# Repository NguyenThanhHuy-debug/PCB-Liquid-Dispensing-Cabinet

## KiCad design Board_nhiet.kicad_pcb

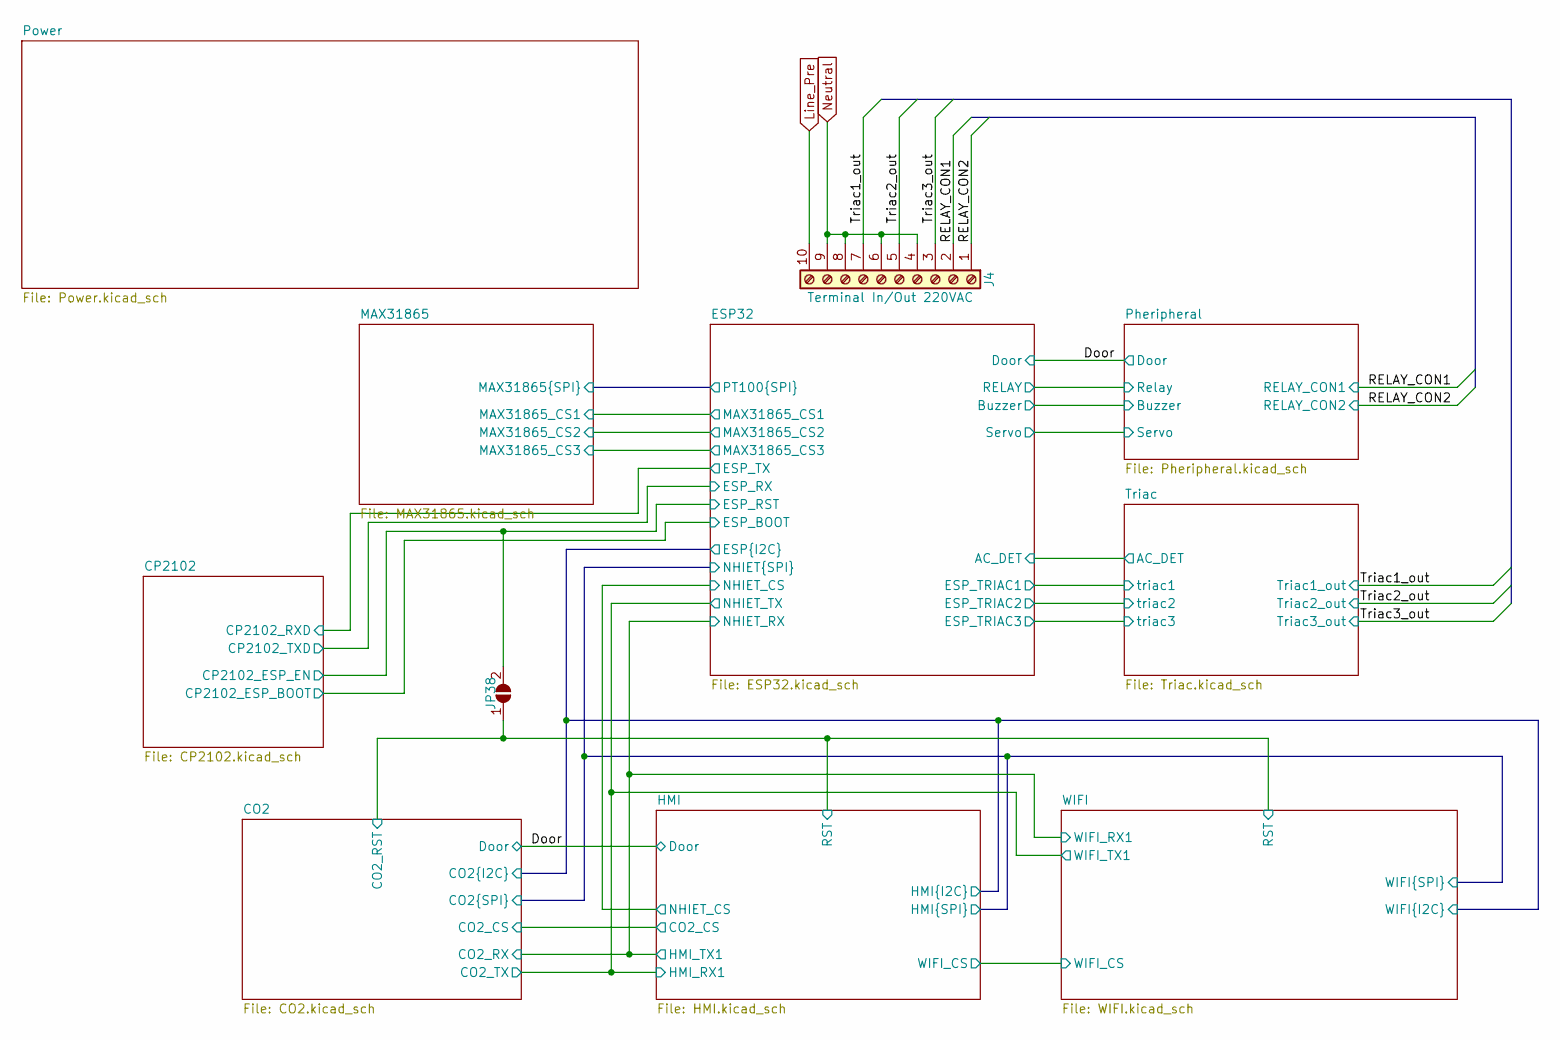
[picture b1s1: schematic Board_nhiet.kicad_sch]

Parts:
J4: Terminal In/Out 220VAC; TerminalBlock_Screw_HB9500_10P_P9.5mm
JP38: SolderJumper_2_Open; SolderJumper-2_P1.3mm_Open_RoundedPad1.0x1.5mm

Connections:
/CO2/CO2_RST: JP38.1 (A); also elsewhere on the board
/ESP32/ESP_RST: JP38.2 (B); also elsewhere on the board
/RELAY_CON1: J4.2; also elsewhere on the board
/RELAY_CON2: J4.1; also elsewhere on the board
/Triac1_out: J4.7; also elsewhere on the board
/Triac2_out: J4.5; also elsewhere on the board
/Triac3_out: J4.3; also elsewhere on the board
Line_Pre: J4.10; also elsewhere on the board
Neutral: J4.4, J4.6, J4.8, J4.9; also elsewhere on the board

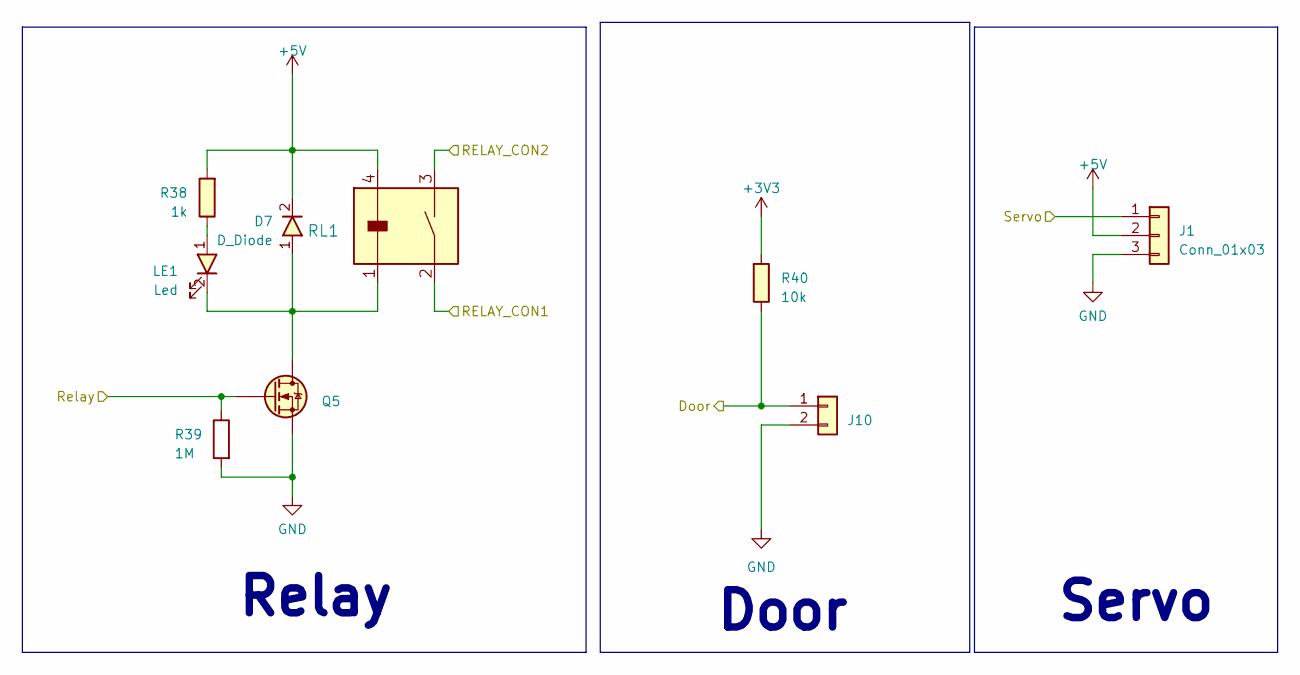
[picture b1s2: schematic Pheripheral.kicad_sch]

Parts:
D7: D_Diode; D_SOD-123
J1: Conn_01x03; Terminal_HT-3.96mm-3P-Vertical-Pluggable
J10: Conn_01x02; Terminal_HT-3.96mm-2P-Vertical-Pluggable
LE1: Led; LED_0603
Q5: N_Mosfet; SOT23-3
R38: 1k; R_0603
R39: 1M; R_0603
R40: 10k; R_0603
RL1: Relay_G5NB-1A-E_DC5; Relay_G5NB-1A-E DC5

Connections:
+3.3V: R40.1; also elsewhere on the board
+5V: D7.2, J1.2, R38.1, RL1.4; also elsewhere on the board
/Door: J10.1, R40.2; also elsewhere on the board
/ESP32/RELAY: Q5.1 (G), R39.1; also elsewhere on the board
/ESP32/Servo: J1.1; also elsewhere on the board
/RELAY_CON1: RL1.2; also elsewhere on the board
/RELAY_CON2: RL1.3; also elsewhere on the board
GND: J1.3, J10.2, Q5.2 (S), R39.2; also elsewhere on the board
unnamed: LE1.1, R38.2
unnamed: D7.1, LE1.2, Q5.3 (D), RL1.1

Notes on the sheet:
Relay
Servo
Door

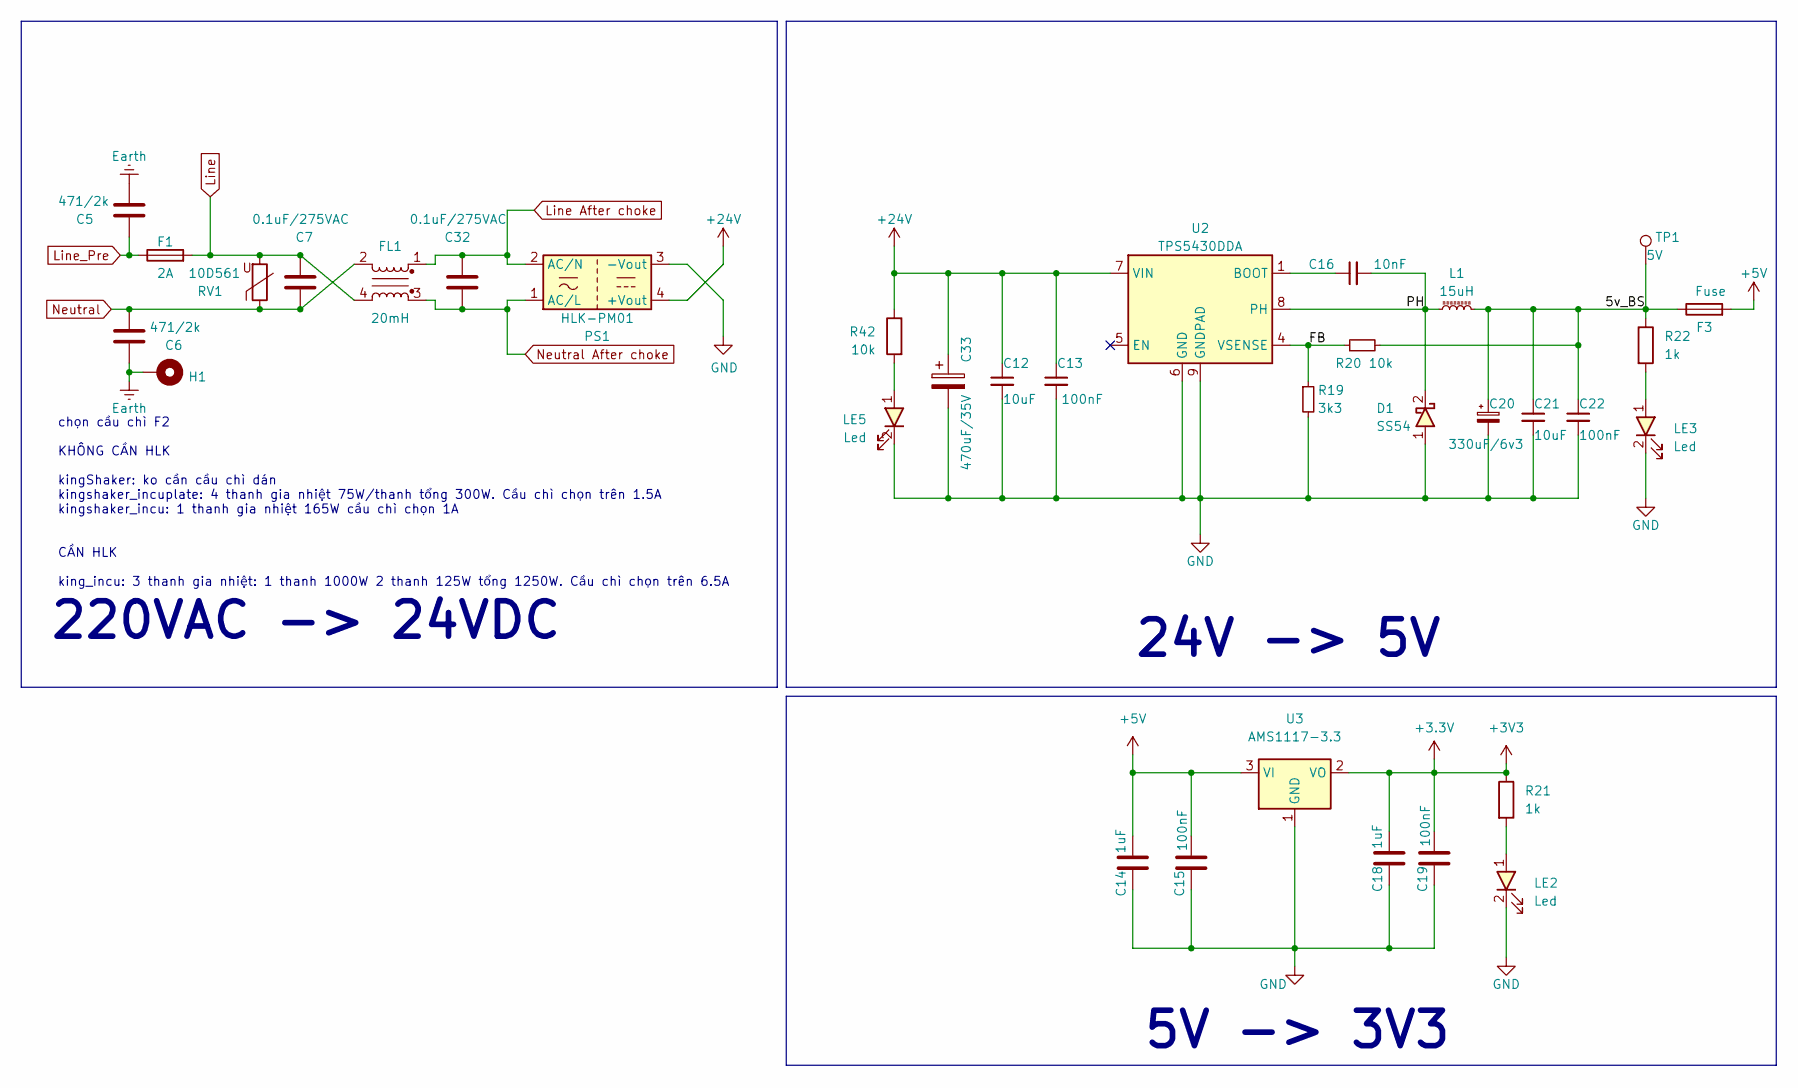
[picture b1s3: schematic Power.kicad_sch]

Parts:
C5, C6: 471/2k; C_Disc_D4.3mm_W1.9mm_P5.00mm
C7, C32: 0.1uF/275VAC; C_Rect_L16.5mm_W5.0mm_P15.00mm_MKT
C12, C21: 10uF; C_0805
C13, C22: 100nF; C_0805
C14, C18: 1uF; C_0603
C15, C19: 100nF; C_0603
C16: 10nF; C_0603
C20: 330uF/6v3; CP_Elec_6.3x7.7
C33: 470uF/35V; CP_Elec_10x10.5
D1: SS54; D_SMA
F1: 2A; Fuse_HolderGlass5x20mm
F3: Fuse; Fuse_1812_4532Metric
FL1: 20mH; ACFilterChokeUU9.8
H1: MountingHole_Pad; MountingHole_3.2mm_M3_Pad_Via
L1: 15uH; L_6.6x6.6
LE2, LE3, LE5: Led; LED_0603
PS1: HLK-PM01; ACDC_HLK-20MXX
R19: 3k3; R_0603
R20, R42: 10k; R_0603
R21, R22: 1k; R_0603
RV1: 10D561; RV_Disc_D12mm_W5.8mm_P7.5mm
TP1: 5V; TestPoint_Pad_D1.0mm
U2: TPS5430DDA; SOIC8E(EXPOSED PAD)
U3: AMS1117-3.3; SOT-223-3_TabPin2

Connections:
+3.3V: C18.2, C19.2, R21.1, U3.2 (VO); also elsewhere on the board
+5V: C14.2, C15.2, F3.2, U3.3 (VI); also elsewhere on the board
+24V: C12.1, C13.1, C33.1, PS1.4 (+Vout), R42.1, U2.7 (VIN); also elsewhere on the board
/Power/5v_BS: C20.1, C21.1, C22.1, F3.1, L1.2, R20.2, R22.1, TP1.1
/Power/FB: R19.1, R20.1, U2.4 (VSENSE)
/Power/PH: C16.2, D1.2, L1.1, U2.8 (PH)
Earth: C5.2, C6.1, H1.1
GND: C12.2, C13.2, C14.1, C15.1, C18.1, C19.1, C20.2, C21.2, C22.2, C33.2, D1.1, LE2.2, LE3.2, LE5.2, PS1.3 (-Vout), R19.2, U2.6 (GND), U2.9 (GNDPAD), U3.1 (GND); also elsewhere on the board
Line: C7.2, F1.2, FL1.4, RV1.2
Line After choke: C32.2, FL1.1, PS1.2 (AC/N); also elsewhere on the board
Line_Pre: C5.1, F1.1; also elsewhere on the board
unnamed: LE2.1, R21.2
unnamed: LE3.1, R22.2
unnamed: LE5.1, R42.2
unnamed: C16.1, U2.1 (BOOT)
Neutral: C6.2, C7.1, FL1.2, RV1.1; also elsewhere on the board
Neutral After choke: C32.1, FL1.3, PS1.1 (AC/L); also elsewhere on the board

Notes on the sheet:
chọn cầu chì F2 KHÔNG CẦN HLK kingShaker: ko cần cầu chì dán kingshaker_incuplate: 4 thanh gia nhiệt 75W/thanh tổng 300W. Cầu chì chọn trên 1.5A kingshaker_incu: 1 thanh gia nhiệt 165W cầu chì chọn 1A CẦN HLK king_incu: 3 thanh gia nhiệt: 1 thanh 1000W 2 thanh 125W tổng 1250W. Cầu chì chọn trên 6.5A
220VAC -> 24VDC
5V -> 3V3
24V -> 5V

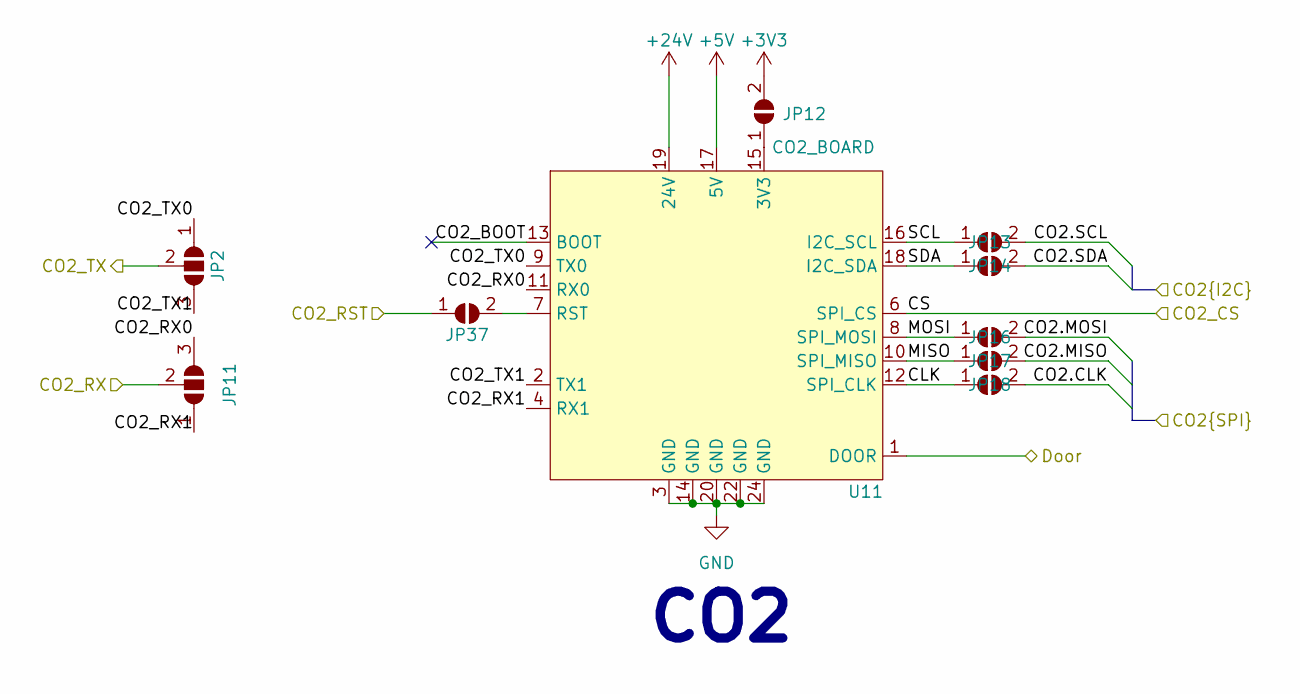
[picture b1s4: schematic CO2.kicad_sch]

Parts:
JP2, JP11: SolderJumper_3_Open; SolderJumper-3_P1.3mm_Open_RoundedPad1.0x1.5mm_NumberLabels
JP12, JP13, JP14, JP16, JP17, JP18, JP37: SolderJumper_2_Open; SolderJumper-2_P1.3mm_Open_RoundedPad1.0x1.5mm
U11: CO2_BOARD; CO2_Board

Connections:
+3.3V: JP12.2 (B); also elsewhere on the board
+5V: U11.17 (5V); also elsewhere on the board
+24V: U11.19 (24V), U11.21 (24V), U11.23 (24V); also elsewhere on the board
/CO2/CLK: JP18.1 (A), U11.12 (SPI_CLK)
/CO2/CO2.CLK: JP18.2 (B); also elsewhere on the board
/CO2/CO2.MISO: JP17.2 (B); also elsewhere on the board
/CO2/CO2.MOSI: JP16.2 (B); also elsewhere on the board
/CO2/CO2.SCL: JP13.2 (B); also elsewhere on the board
/CO2/CO2.SDA: JP14.2 (B); also elsewhere on the board
/CO2/CO2_BOOT: U11.13 (BOOT)
/CO2/CO2_RST: JP37.1 (A); also elsewhere on the board
/CO2/CO2_RX: JP11.2 (C); also elsewhere on the board
/CO2/CO2_RX0: JP11.3 (B), U11.11 (RX0)
/CO2/CO2_RX1: JP11.1 (A), U11.4 (RX1)
/CO2/CO2_TX: JP2.2 (C); also elsewhere on the board
/CO2/CO2_TX0: JP2.1 (A), U11.9 (TX0)
/CO2/CO2_TX1: JP2.3 (B), U11.2 (TX1)
/CO2/CS: U11.6 (SPI_CS); also elsewhere on the board
/CO2/MISO: JP17.1 (A), U11.10 (SPI_MISO)
/CO2/MOSI: JP16.1 (A), U11.8 (SPI_MOSI)
/CO2/SCL: JP13.1 (A), U11.16 (I2C_SCL)
/CO2/SDA: JP14.1 (A), U11.18 (I2C_SDA)
/Door: U11.1 (DOOR); also elsewhere on the board
GND: U11.3 (GND), U11.5 (GND), U11.14 (GND), U11.20 (GND), U11.22 (GND), U11.24 (GND); also elsewhere on the board
unnamed: JP12.1 (A), U11.15 (3V3)
unnamed: JP37.2 (B), U11.7 (RST)

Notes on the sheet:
CO2

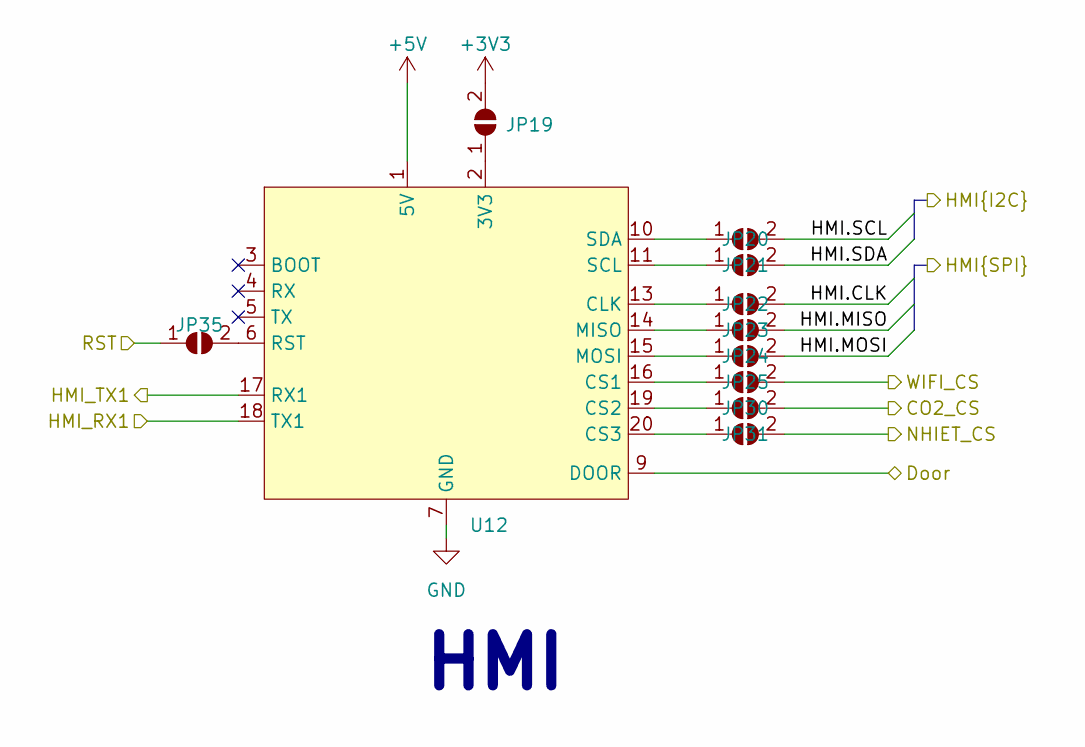
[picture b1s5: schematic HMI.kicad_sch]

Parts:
JP19, JP20, JP21, JP22, JP23, JP24, JP25, JP30, JP31, JP35: SolderJumper_2_Open; SolderJumper-2_P1.3mm_Open_RoundedPad1.0x1.5mm
U12: HMI_BOARD

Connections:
+3.3V: JP19.2 (B); also elsewhere on the board
+5V: U12.1 (5V); also elsewhere on the board
/CO2/CO2.CLK: JP22.2 (B); also elsewhere on the board
/CO2/CO2.MISO: JP23.2 (B); also elsewhere on the board
/CO2/CO2.MOSI: JP24.2 (B); also elsewhere on the board
/CO2/CO2.SCL: JP20.2 (B); also elsewhere on the board
/CO2/CO2.SDA: JP21.2 (B); also elsewhere on the board
/CO2/CO2_RST: JP35.1 (A); also elsewhere on the board
/CO2/CO2_RX: U12.17 (RX1); also elsewhere on the board
/CO2/CO2_TX: U12.18 (TX1); also elsewhere on the board
/CO2/CS: JP30.2 (B); also elsewhere on the board
/Door: U12.9 (DOOR); also elsewhere on the board
/ESP32/NHIET_CS: JP31.2 (B); also elsewhere on the board
/HMI/WIFI_CS: JP25.2 (B); also elsewhere on the board
GND: U12.7 (GND), U12.8 (GND), U12.12 (GND); also elsewhere on the board
unnamed: JP19.1 (A), U12.2 (3V3)
unnamed: JP20.1 (A), U12.10 (SDA)
unnamed: JP21.1 (A), U12.11 (SCL)
unnamed: JP22.1 (A), U12.13 (CLK)
unnamed: JP23.1 (A), U12.14 (MISO)
unnamed: JP24.1 (A), U12.15 (MOSI)
unnamed: JP25.1 (A), U12.16 (CS1)
unnamed: JP30.1 (A), U12.19 (CS2)
unnamed: JP31.1 (A), U12.20 (CS3)
unnamed: JP35.2 (B), U12.6 (RST)

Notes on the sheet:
HMI

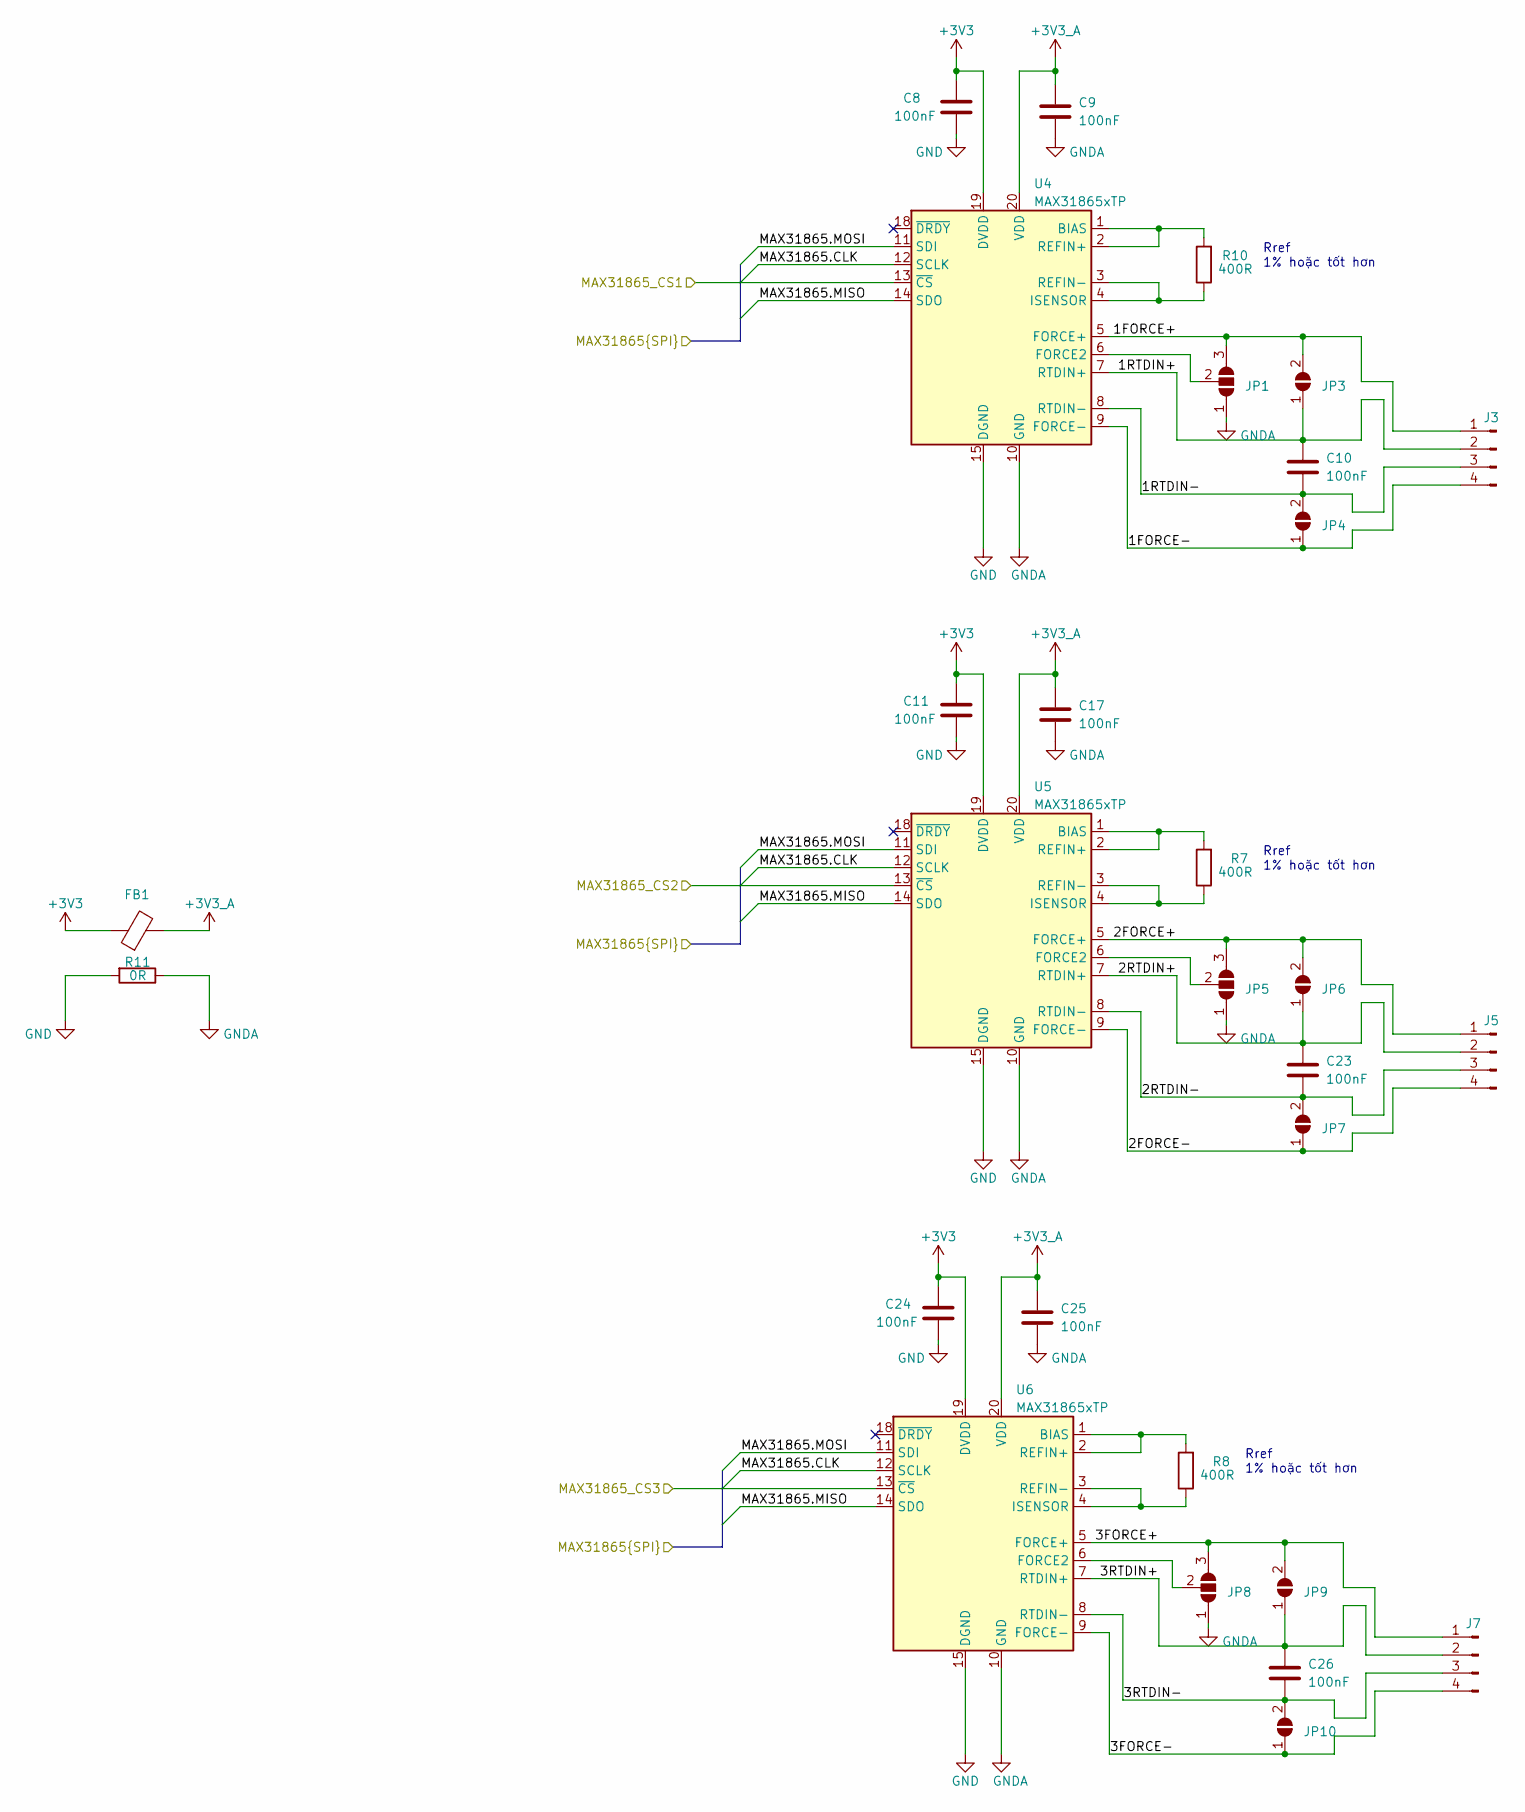
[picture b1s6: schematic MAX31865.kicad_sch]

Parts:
C8, C9, C10, C11, C17, C23, C24, C25, C26: 100nF; C_0603
FB1: FerriteBead; R_0805
J3, J5, J7: Conn_01x04_Pin; Terminal_HT-3.96mm-4P-Vertical-Pluggable
JP1, JP5, JP8: SolderJumper_3_Open; SolderJumper-3_P1.3mm_Bridged12_RoundedPad1.0x1.5mm
JP3, JP4, JP6, JP7, JP9, JP10: SolderJumper_2_Open; SolderJumper-2_P1.3mm_Open_RoundedPad1.0x1.5mm
R7, R8, R10: 400R; R_0805
R11: 0R; R_0603
U4, U5, U6: MAX31865xTP; TQFN-20-1EP_5x5mm_P0.65mm_EP3.25x3.25mm

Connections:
+3.3V: C8.1, C11.1, C24.1, FB1.1, U4.19 (DVDD), U5.19 (DVDD), U6.19 (DVDD); also elsewhere on the board
+3V3_A: C9.1, C17.1, C25.1, FB1.2, U4.20 (VDD), U5.20 (VDD), U6.20 (VDD)
/ESP32/MAX31865_CS1: U4.13 (~CS); also elsewhere on the board
/ESP32/MAX31865_CS2: U5.13 (~CS); also elsewhere on the board
/ESP32/MAX31865_CS3: U6.13 (~CS); also elsewhere on the board
/ESP32/PT100.CLK: U4.12 (SCLK), U5.12 (SCLK), U6.12 (SCLK); also elsewhere on the board
/ESP32/PT100.MISO: U4.14 (SDO), U5.14 (SDO), U6.14 (SDO); also elsewhere on the board
/ESP32/PT100.MOSI: U4.11 (SDI), U5.11 (SDI), U6.11 (SDI); also elsewhere on the board
/MAX31865/1FORCE+: J3.1, JP1.3 (B), JP3.2 (B), U4.5 (FORCE+)
/MAX31865/1FORCE-: J3.4, JP4.1 (A), U4.9 (FORCE-)
/MAX31865/1RTDIN+: C10.1, J3.2, JP3.1 (A), U4.7 (RTDIN+)
/MAX31865/1RTDIN-: C10.2, J3.3, JP4.2 (B), U4.8 (RTDIN-)
/MAX31865/2FORCE+: J5.1, JP5.3 (B), JP6.2 (B), U5.5 (FORCE+)
/MAX31865/2FORCE-: J5.4, JP7.1 (A), U5.9 (FORCE-)
/MAX31865/2RTDIN+: C23.1, J5.2, JP6.1 (A), U5.7 (RTDIN+)
/MAX31865/2RTDIN-: C23.2, J5.3, JP7.2 (B), U5.8 (RTDIN-)
/MAX31865/3FORCE+: J7.1, JP8.3 (B), JP9.2 (B), U6.5 (FORCE+)
/MAX31865/3FORCE-: J7.4, JP10.1 (A), U6.9 (FORCE-)
/MAX31865/3RTDIN+: C26.1, J7.2, JP9.1 (A), U6.7 (RTDIN+)
/MAX31865/3RTDIN-: C26.2, J7.3, JP10.2 (B), U6.8 (RTDIN-)
GND: C8.2, C11.2, C24.2, R11.2, U4.15 (DGND), U5.15 (DGND), U6.15 (DGND); also elsewhere on the board
GNDA: C9.2, C17.2, C25.2, JP1.1 (A), JP5.1 (A), JP8.1 (A), R11.1, U4.10 (GND), U4.16 (GND), U4.21 (GND), U5.10 (GND), U5.16 (GND), U5.21 (GND), U6.10 (GND), U6.16 (GND), U6.21 (GND)
unnamed: JP1.2 (C), U4.6 (FORCE2)
unnamed: JP5.2 (C), U5.6 (FORCE2)
unnamed: JP8.2 (C), U6.6 (FORCE2)
unnamed: R10.2, U4.1 (BIAS), U4.2 (REFIN+)
unnamed: R10.1, U4.3 (REFIN-), U4.4 (ISENSOR)
unnamed: R7.2, U5.1 (BIAS), U5.2 (REFIN+)
unnamed: R7.1, U5.3 (REFIN-), U5.4 (ISENSOR)
unnamed: R8.2, U6.1 (BIAS), U6.2 (REFIN+)
unnamed: R8.1, U6.3 (REFIN-), U6.4 (ISENSOR)

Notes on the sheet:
Rref 1% hoặc tốt hơn

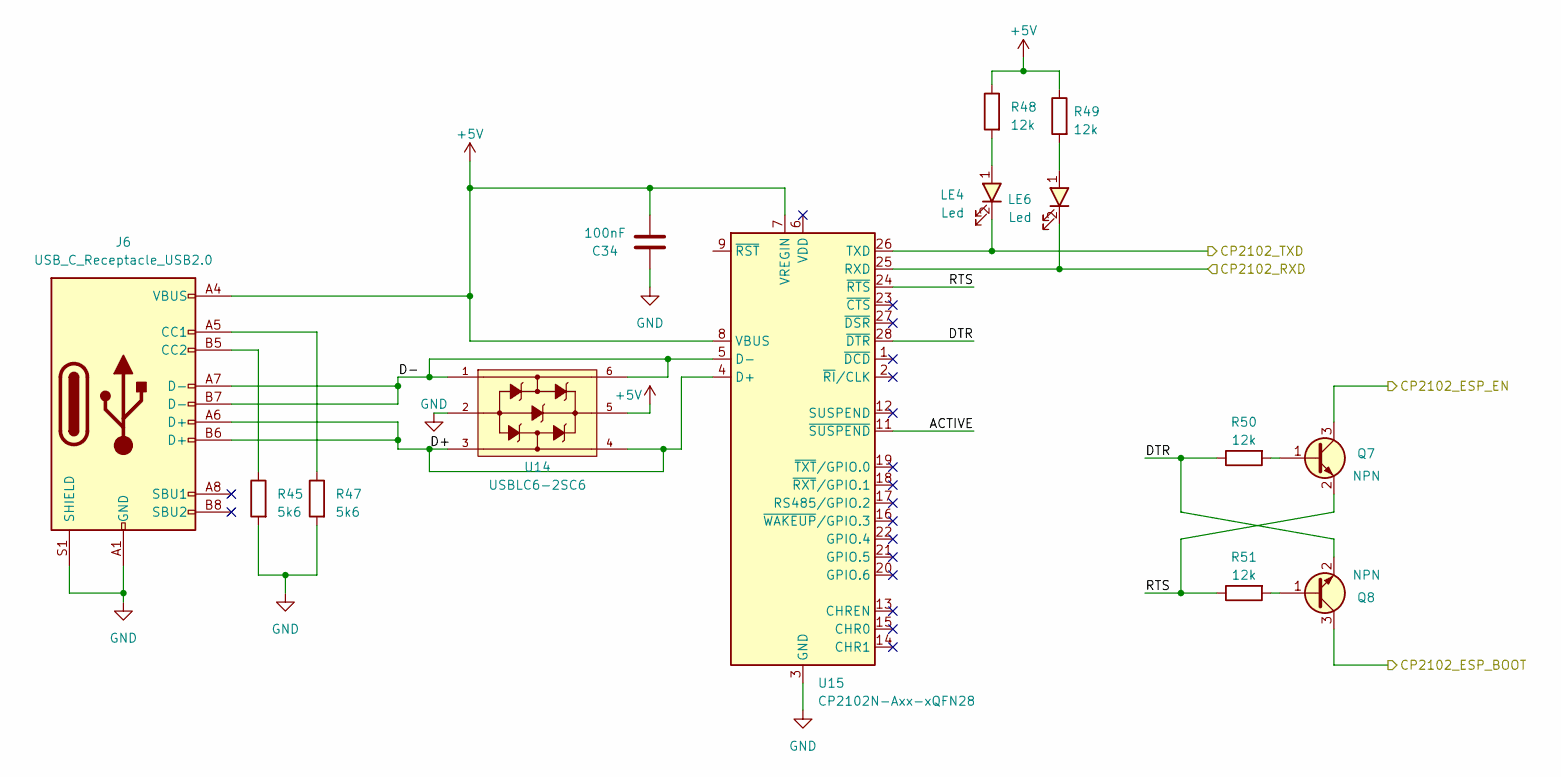
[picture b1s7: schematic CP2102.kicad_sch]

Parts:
C34: 100nF; C_0603
J6: USB_C_Receptacle_USB2.0; USB_C_Receptacle_XKB_U262-16XN-4BVC11
LE4, LE6: Led; LED_0603
Q7, Q8: NPN; SOT23-3
R45, R47: 5k6; R_0603
R48, R49, R50, R51: 12k; R_0603
U14: USBLC6-2SC6; SOT23-6
U15: CP2102N-Axx-xQFN28; QFN-28_5x5_PAD

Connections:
+5V: C34.2, J6.A4 (VBUS), J6.A9 (VBUS), J6.B4 (VBUS), J6.B9 (VBUS), R48.1, R49.1, U14.5, U15.7 (VREGIN), U15.8 (VBUS); also elsewhere on the board
/CP2102/ACTIVE: U15.11 (~SUSPEND)
/CP2102/D+: J6.A6 (D+), J6.B6 (D+), U14.3, U14.4, U15.4 (D+)
/CP2102/D-: J6.A7 (D-), J6.B7 (D-), U14.1, U14.6, U15.5 (D-)
/CP2102/DTR: Q8.2 (E), R50.1, U15.28 (~DTR)
/CP2102/RTS: Q7.2 (E), R51.1, U15.24 (~RTS)
/ESP32/ESP_BOOT: Q8.3 (C); also elsewhere on the board
/ESP32/ESP_RST: Q7.3 (C); also elsewhere on the board
/ESP32/ESP_RX: LE4.2, U15.26 (TXD); also elsewhere on the board
/ESP32/ESP_TX: LE6.2, U15.25 (RXD); also elsewhere on the board
GND: C34.1, J6.A1 (GND), J6.A12 (GND), J6.B1 (GND), J6.B12 (GND), J6.S1 (SHIELD), R45.2, R47.2, U14.2, U15.3 (GND), U15.29 (GND); also elsewhere on the board
unnamed: J6.A5 (CC1), R47.1
unnamed: J6.B5 (CC2), R45.1
unnamed: LE4.1, R48.2
unnamed: LE6.1, R49.2
unnamed: Q7.1 (B), R50.2
unnamed: Q8.1 (B), R51.2

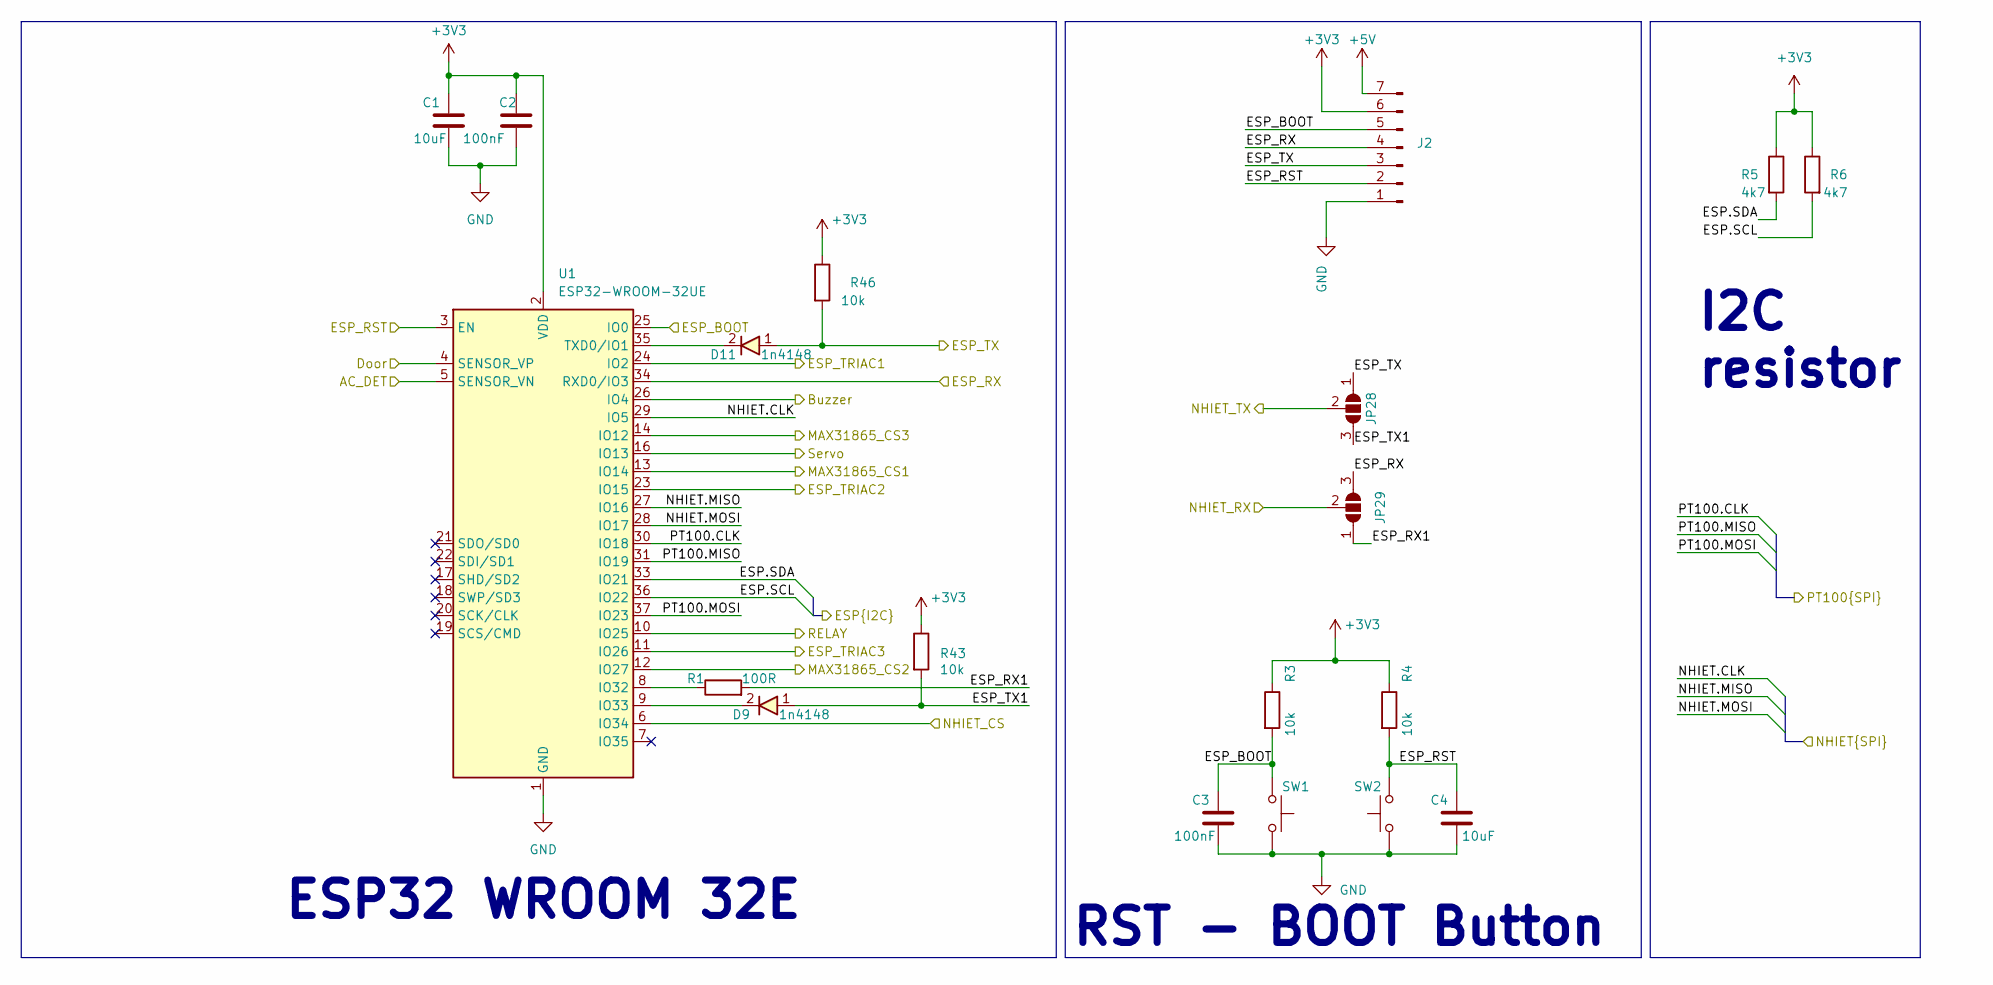
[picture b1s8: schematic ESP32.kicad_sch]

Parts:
C1, C4: 10uF; C_0603
C2, C3: 100nF; C_0603
D9, D11: 1n4148; D_SOD323
J2: Conn_01x07_Pin; Conn_XH-P2.54mm-7P
JP28, JP29: SolderJumper_3_Open; SolderJumper-3_P1.3mm_Open_RoundedPad1.0x1.5mm_NumberLabels
R1: 100R; R_0603
R3, R4, R43, R46: 10k; R_0603
R5, R6: 4k7; R_0603
SW1, SW2: SW_Push; SW_SPST_PTS810
U1: ESP32-WROOM-32UE; ESP32-WROOM-32E

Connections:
+3.3V: C1.1, C2.1, J2.6, R3.1, R4.1, R5.1, R6.1, R43.1, R46.1, U1.2 (VDD); also elsewhere on the board
+5V: J2.7; also elsewhere on the board
/CO2/CO2.CLK: U1.29 (IO5); also elsewhere on the board
/CO2/CO2.MISO: U1.27 (IO16); also elsewhere on the board
/CO2/CO2.MOSI: U1.28 (IO17); also elsewhere on the board
/CO2/CO2.SCL: R6.2, U1.36 (IO22); also elsewhere on the board
/CO2/CO2.SDA: R5.2, U1.33 (IO21); also elsewhere on the board
/CO2/CO2_RX: JP29.2 (C); also elsewhere on the board
/CO2/CO2_TX: JP28.2 (C); also elsewhere on the board
/Door: U1.4 (SENSOR_VP); also elsewhere on the board
/ESP32/AC_DET: U1.5 (SENSOR_VN); also elsewhere on the board
/ESP32/Buzzer: U1.26 (IO4)
/ESP32/ESP_BOOT: C3.1, J2.5, R3.2, SW1.1, U1.25 (IO0); also elsewhere on the board
/ESP32/ESP_RST: C4.1, J2.2, R4.2, SW2.2, U1.3 (EN); also elsewhere on the board
/ESP32/ESP_RX: J2.4, JP29.3 (B), U1.34 (RXD0/IO3); also elsewhere on the board
/ESP32/ESP_RX1: JP29.1 (A), R1.2
/ESP32/ESP_TRIAC1: U1.24 (IO2); also elsewhere on the board
/ESP32/ESP_TRIAC2: U1.23 (IO15); also elsewhere on the board
/ESP32/ESP_TRIAC3: U1.11 (IO26); also elsewhere on the board
/ESP32/ESP_TX: D11.1, J2.3, JP28.1 (A), R46.2; also elsewhere on the board
/ESP32/ESP_TX1: D9.1, JP28.3 (B), R43.2
/ESP32/MAX31865_CS1: U1.13 (IO14); also elsewhere on the board
/ESP32/MAX31865_CS2: U1.12 (IO27); also elsewhere on the board
/ESP32/MAX31865_CS3: U1.14 (IO12); also elsewhere on the board
/ESP32/NHIET_CS: U1.6 (IO34); also elsewhere on the board
/ESP32/PT100.CLK: U1.30 (IO18); also elsewhere on the board
/ESP32/PT100.MISO: U1.31 (IO19); also elsewhere on the board
/ESP32/PT100.MOSI: U1.37 (IO23); also elsewhere on the board
/ESP32/RELAY: U1.10 (IO25); also elsewhere on the board
/ESP32/Servo: U1.16 (IO13); also elsewhere on the board
GND: C1.2, C2.2, C3.2, C4.2, J2.1, SW1.2, SW2.1, U1.1 (GND), U1.15 (GND), U1.38 (GND), U1.39 (GND); also elsewhere on the board
unnamed: R1.1, U1.8 (IO32)
unnamed: D9.2, U1.9 (IO33)
unnamed: D11.2, U1.35 (TXD0/IO1)

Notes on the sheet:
I2C resistor
ESP32 WROOM 32E
RST - BOOT Button

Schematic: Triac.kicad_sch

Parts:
C27, C28, C31: 0.01uF; C_Disc_D12.5mm_W5.0mm_P10.00mm
C29: 10uF; D_DO-35_SOD27_P7.62mm_Horizontal
C30: 10nF; C_0805
D2, D6: TRIAC; TO-220-3_Vertical_heatsink_cutBoard
D3: TRIAC; TO-220-3_Vertical_BIG_heatsink_TRIAC
D4: 1N4148; D_SOD323
D5: MB10F; Bridge_MB10F-13
Q1, Q2, Q4: 1AM; SOT23-3
Q3: NPN; SOT23-3
R9, R12, R15, R16, R29, R32: 470R; R_0603
R13, R14, R30: 10k; R_0603
R17, R18, R23, R24, R33, R34: 330R; R_2512
R25, R26, R37: 39R; R_Axial_DIN0414_L11.9mm_D4.5mm_P5.08mm_Vertical
R27, R28: 1k; R_0603
R31: 22k; R_0603
R35, R36: 180k; R_0805
U7, U8, U10: MOC3021; DIL06-SMD
U9: EL357; OPTO_EL357N-G

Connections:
+3.3V: R27.1; also elsewhere on the board
+5V: R15.1, R16.1, R32.1; also elsewhere on the board
/ESP32/AC_DET: R27.2, U9.4; also elsewhere on the board
/ESP32/ESP_TRIAC1: R12.1; also elsewhere on the board
/ESP32/ESP_TRIAC2: R29.1; also elsewhere on the board
/ESP32/ESP_TRIAC3: R9.1; also elsewhere on the board
/Triac1_out: C28.2, D3.1 (A1), R18.1; also elsewhere on the board
/Triac2_out: C31.2, D6.1 (A1), R33.1; also elsewhere on the board
/Triac3_out: C27.2, D2.1 (A1), R17.1; also elsewhere on the board
GND: Q1.2 (E), Q2.2 (E), Q4.2 (E), R13.1, R14.1, R30.1, U9.3; also elsewhere on the board
Line After choke: R35.2; also elsewhere on the board
Line_Pre: D2.2 (A2), D3.2 (A2), D6.2 (A2), R23.2, R24.2, R25.1, R26.1, R34.2, R37.1; also elsewhere on the board
unnamed: C27.1, R25.2
unnamed: C28.1, R26.2
unnamed: C30.1, D5.4, R35.1
unnamed: C30.2, D5.2, R36.1
unnamed: C31.1, R37.2
unnamed: D2.3 (G), R17.2, U7.4
unnamed: D3.3 (G), R18.2, U8.4
unnamed: C29.1, D5.1 (+), R28.2, R31.1
unnamed: D4.2, D5.3 (-), Q3.1 (B), R31.2
unnamed: D6.3 (G), R33.2, U10.4
unnamed: Q1.1 (B), R9.2, R13.2
unnamed: Q1.3 (C), U7.2
unnamed: Q2.1 (B), R12.2, R14.2
unnamed: Q2.3 (C), U8.2
unnamed: Q3.3 (C), U9.2
unnamed: C29.2, D4.1, Q3.2 (E)
unnamed: Q4.1 (B), R29.2, R30.2
unnamed: Q4.3 (C), U10.2
unnamed: R15.2, U7.1
unnamed: R16.2, U8.1
unnamed: R23.1, U7.6
unnamed: R24.1, U8.6
unnamed: R28.1, U9.1
unnamed: R32.2, U10.1
unnamed: R34.1, U10.6
Neutral After choke: R36.2; also elsewhere on the board

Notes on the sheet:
ACDET
TRIAC3
TRIAC2
TRIAC1

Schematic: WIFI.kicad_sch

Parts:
D10: 1n4148; D_SOD323
JP26, JP27, JP32, JP33, JP34, JP36: SolderJumper_2_Open; SolderJumper-2_P1.3mm_Open_RoundedPad1.0x1.5mm
R2: 100R; R_0603
R44: 10k; R_0603
U13: DevKitESP32; kitEsp32Rebuild

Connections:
+5V: U13.19 (5V); also elsewhere on the board
/CO2/CO2.CLK: JP33.2 (B); also elsewhere on the board
/CO2/CO2.MISO: JP32.2 (B); also elsewhere on the board
/CO2/CO2.MOSI: JP34.2 (B); also elsewhere on the board
/CO2/CO2.SCL: JP27.2 (B); also elsewhere on the board
/CO2/CO2.SDA: JP26.2 (B); also elsewhere on the board
/CO2/CO2_RST: JP36.1 (A); also elsewhere on the board
/CO2/CO2_RX: R2.2; also elsewhere on the board
/CO2/CO2_TX: D10.1, R44.2; also elsewhere on the board
/HMI/WIFI_CS: U13.3 (SP); also elsewhere on the board
GND: U13.14 (GND), U13.18 (GND), U13.20 (GND), U13.26 (GND); also elsewhere on the board
unnamed: JP26.1 (A), U13.25 (21)
unnamed: JP27.1 (A), U13.22
unnamed: JP32.1 (A), U13.27 (19)
unnamed: JP33.1 (A), U13.28 (18)
unnamed: JP34.1 (A), U13.21 (23)
unnamed: JP36.2 (B), U13.2 (EN)
unnamed: R44.1, U13.1 (3V)
unnamed: R2.1, U13.7 (32)
unnamed: D10.2, U13.8 (33)

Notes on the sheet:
WiFi

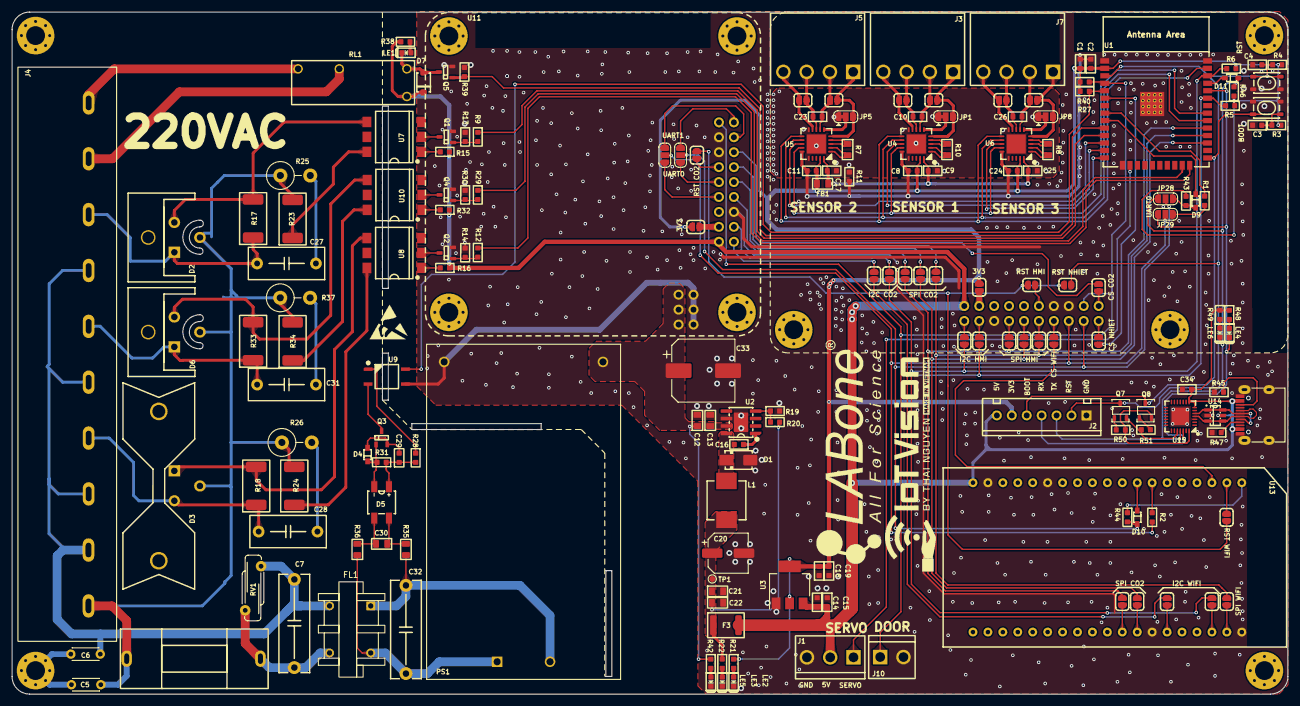
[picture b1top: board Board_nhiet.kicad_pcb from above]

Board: 2 copper layers, 217.0 x 116.0 mm, 179 parts (0 on the bottom side), 145 nets.

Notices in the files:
parts and their libraries:
Copyright 2021 Accelerated Designs. All rights reserved.
